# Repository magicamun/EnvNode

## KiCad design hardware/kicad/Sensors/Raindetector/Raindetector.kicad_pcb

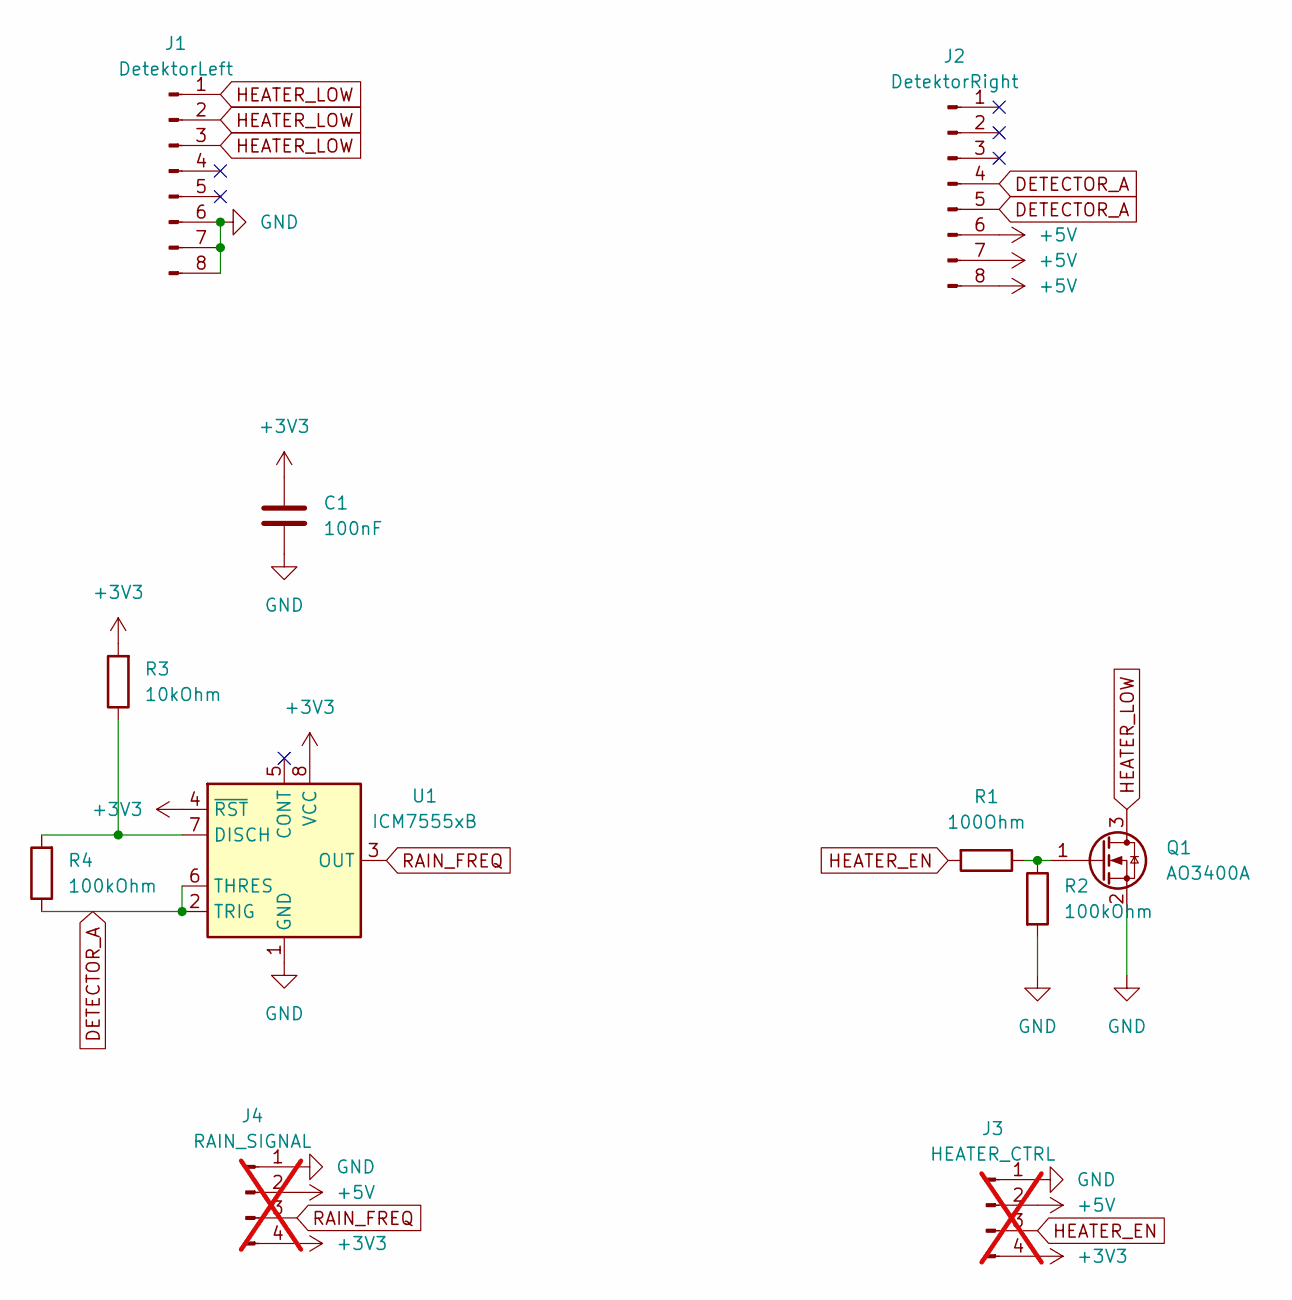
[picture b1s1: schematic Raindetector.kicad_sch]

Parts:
C1: 100nF; C_1206_3216Metric_Pad1.33x1.80mm_HandSolder
J1: DetektorLeft; PinHeader_1x08_P2.54mm_Vertical
J2: DetektorRight; PinHeader_1x08_P2.54mm_Vertical
J3: HEATER_CTRL; PinHeader_1x04_P2.54mm_Vertical; not fitted
J4: RAIN_SIGNAL; PinHeader_1x04_P2.54mm_Vertical; not fitted
Q1: AO3400A; SOT-23
R1: 100Ohm; R_1206_3216Metric_Pad1.30x1.75mm_HandSolder
R2, R4: 100kOhm; R_1206_3216Metric_Pad1.30x1.75mm_HandSolder
R3: 10kOhm; R_1206_3216Metric_Pad1.30x1.75mm_HandSolder
U1: ICM7555xB; SOIC-8_3.9x4.9mm_P1.27mm

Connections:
+3V3: C1.1, J3.4, J4.4, R3.2, U1.4 (~RST), U1.8 (VCC)
+5V: J2.6, J2.7, J2.8, J3.2, J4.2
DETECTOR_A: J2.4, J2.5, R4.1, U1.2 (TRIG), U1.6 (THRES)
GND: C1.2, J1.6, J1.7, J1.8, J3.1, J4.1, Q1.2 (S), R2.2, U1.1 (GND)
HEATER_EN: J3.3, R1.2
HEATER_LOW: J1.1, J1.2, J1.3, Q1.3 (D)
unnamed: Q1.1 (G), R1.1, R2.1
unnamed: R3.1, R4.2, U1.7 (DISCH)
RAIN_FREQ: J4.3, U1.3 (OUT)

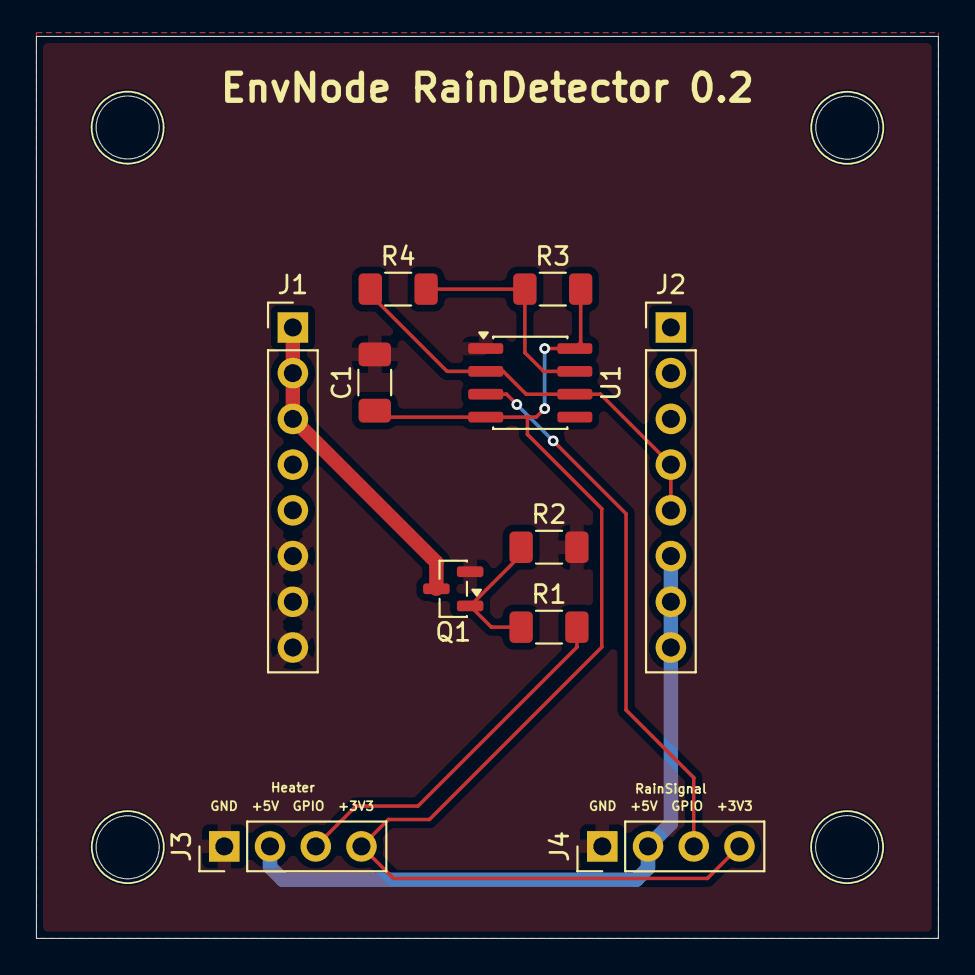
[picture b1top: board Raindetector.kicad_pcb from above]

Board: 2 copper layers, 50.1 x 50.1 mm, 11 parts (0 on the bottom side), 9 nets.

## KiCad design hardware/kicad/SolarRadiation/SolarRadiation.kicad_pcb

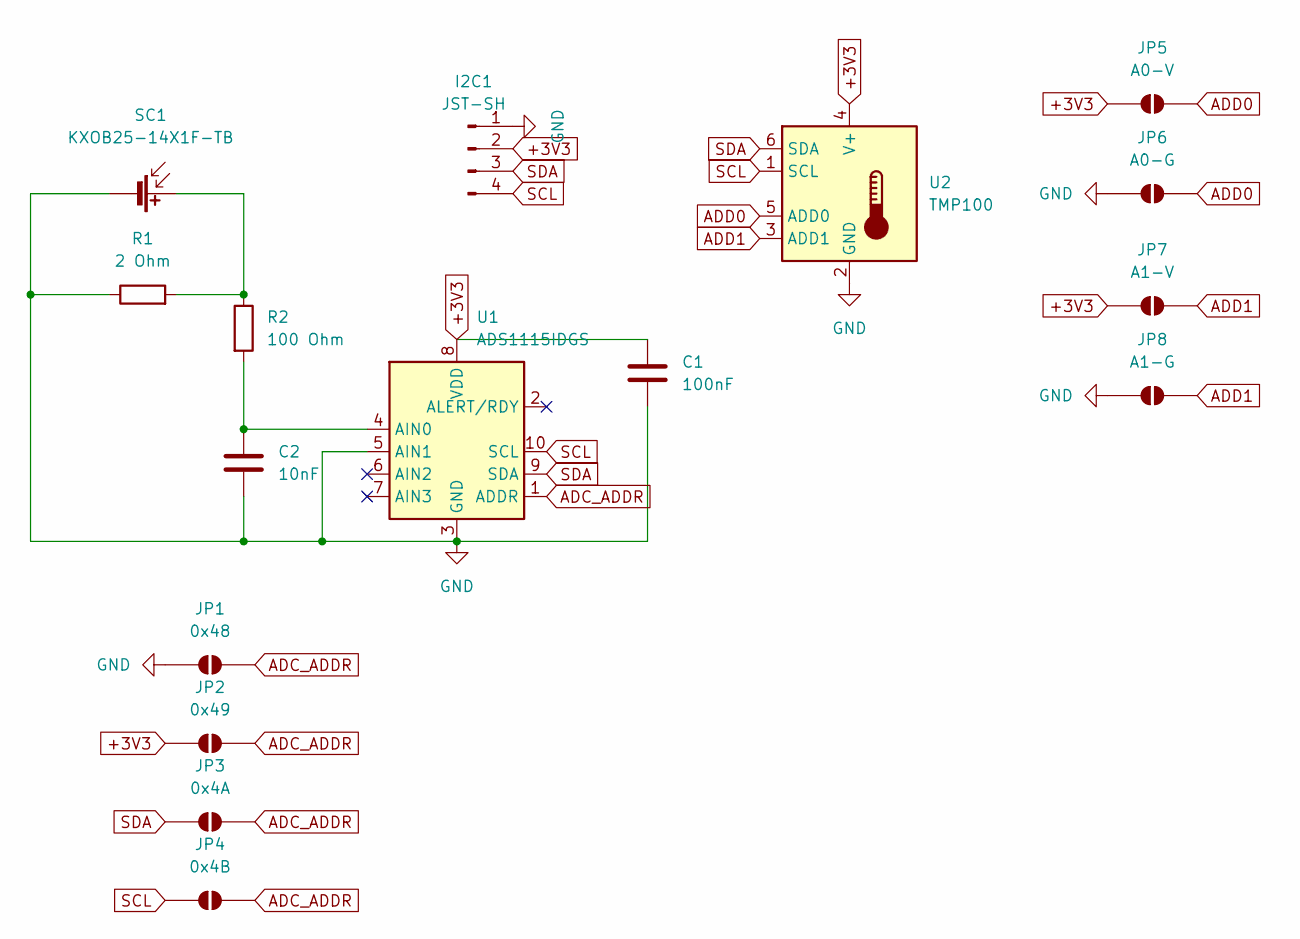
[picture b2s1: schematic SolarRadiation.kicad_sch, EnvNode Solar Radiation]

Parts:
C1: 100nF; C_1206_3216Metric_Pad1.33x1.80mm_HandSolder
C2: 10nF; C_1206_3216Metric_Pad1.33x1.80mm_HandSolder
I2C1: JST-SH; JST_SH_SM04B-SRSS-TB_1x04-1MP_P1.00mm_Horizontal
JP1: 0x48; SolderJumper-2_P1.3mm_Open_Pad1.0x1.5mm
JP2: 0x49; SolderJumper-2_P1.3mm_Open_Pad1.0x1.5mm
JP3: 0x4A; SolderJumper-2_P1.3mm_Open_Pad1.0x1.5mm
JP4: 0x4B; SolderJumper-2_P1.3mm_Open_Pad1.0x1.5mm
JP5: A0-V; SolderJumper-2_P1.3mm_Open_Pad1.0x1.5mm
JP6: A0-G; SolderJumper-2_P1.3mm_Open_Pad1.0x1.5mm
JP7: A1-V; SolderJumper-2_P1.3mm_Open_Pad1.0x1.5mm
JP8: A1-G; SolderJumper-2_P1.3mm_Open_Pad1.0x1.5mm
R1: 2 Ohm; R_1206_3216Metric_Pad1.30x1.75mm_HandSolder
R2: 100 Ohm; R_1206_3216Metric_Pad1.30x1.75mm_HandSolder
SC1: KXOB25-14X1F-TB; KXOB25-14X1F
U1: ADS1115IDGS; TSSOP-10_3x3mm_P0.5mm
U2: TMP100; SOT-23-6

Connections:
+3V3: C1.1, I2C1.2, JP2.1 (A), JP5.1 (A), JP7.1 (A), U1.8 (VDD), U2.4 (V+)
ADC_ADDR: JP1.2 (B), JP2.2 (B), JP3.2 (B), JP4.2 (B), U1.1 (ADDR)
ADD0: JP5.2 (B), JP6.2 (B), U2.5 (ADD0)
ADD1: JP7.2 (B), JP8.2 (B), U2.3 (ADD1)
GND: C1.2, C2.2, I2C1.1, JP1.1 (A), JP6.1 (A), JP8.1 (A), R1.1, SC1.2 (-), U1.3 (GND), U1.5 (AIN1), U2.2 (GND)
unnamed: R1.2, R2.1, SC1.1 (+)
unnamed: C2.1, R2.2, U1.4 (AIN0)
SCL: I2C1.4, JP4.1 (A), U1.10 (SCL), U2.1 (SCL)
SDA: I2C1.3, JP3.1 (A), U1.9 (SDA), U2.6 (SDA)

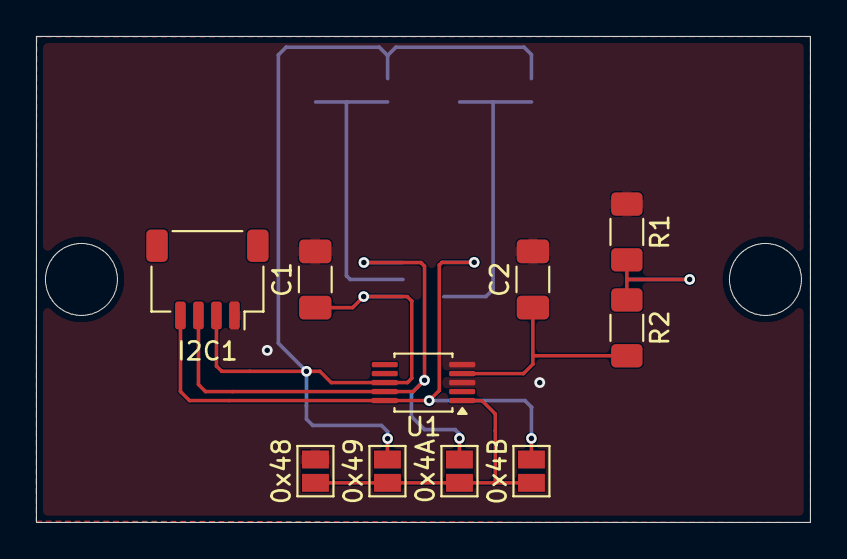
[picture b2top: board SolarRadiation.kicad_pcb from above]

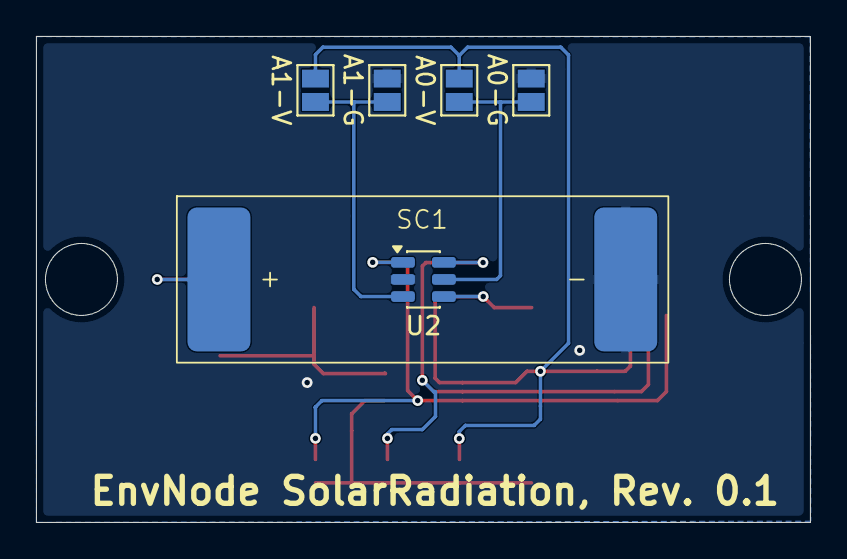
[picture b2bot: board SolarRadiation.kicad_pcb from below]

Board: 2 copper layers, 43.0 x 27.0 mm, 16 parts (6 on the bottom side), 9 nets.

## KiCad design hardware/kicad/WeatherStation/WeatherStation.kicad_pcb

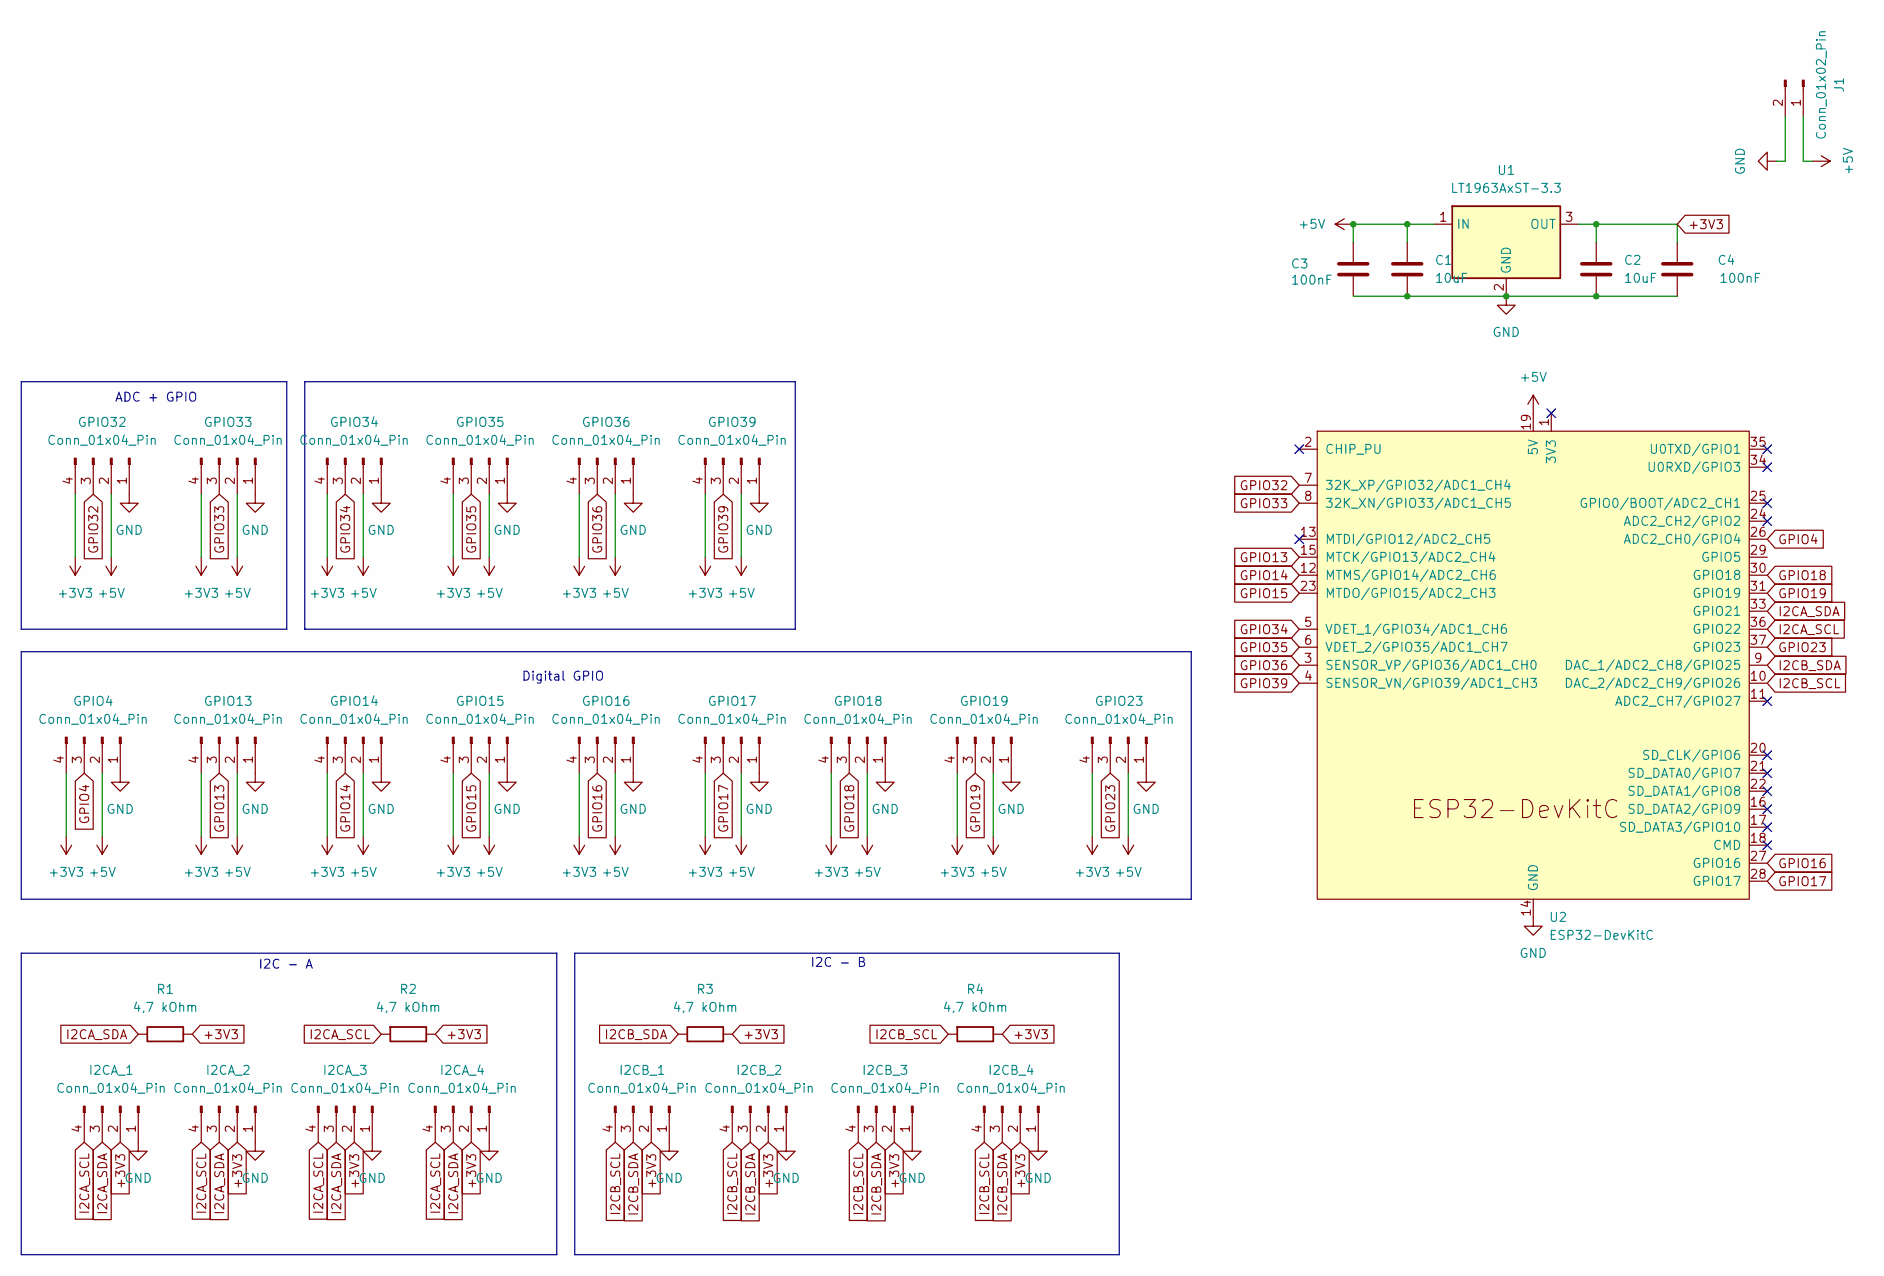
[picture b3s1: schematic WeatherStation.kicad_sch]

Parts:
C1, C2: 10uF; C_1206_3216Metric_Pad1.33x1.80mm_HandSolder
C3, C4: 100nF; C_1206_3216Metric_Pad1.33x1.80mm_HandSolder
GPIO4, GPIO13, GPIO14, GPIO15, GPIO16, GPIO17, GPIO18, GPIO19, GPIO23, GPIO32, GPIO33, GPIO34, GPIO35, GPIO36, GPIO39: Conn_01x04_Pin; JST_PH_B4B-PH-K_1x04_P2.00mm_Vertical
I2CA_1, I2CA_2, I2CA_3, I2CB_1, I2CB_2, I2CB_3: Conn_01x04_Pin; JST_SH_SM04B-SRSS-TB_1x04-1MP_P1.00mm_Horizontal
I2CA_4, I2CB_4: Conn_01x04_Pin; QWIIC_PinSocket_1x04_P2.54mm_Vertical
J1: Conn_01x02_Pin; JST_PH_B2B-PH-K_1x02_P2.00mm_Vertical
R1, R2, R3, R4: 4,7 kOhm; R_1206_3216Metric_Pad1.30x1.75mm_HandSolder
U1: LT1963AxST-3.3; SOT-223-3_TabPin2
U2: ESP32-DevKitC

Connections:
+3V3: C2.1, C4.2, GPIO4.4, GPIO13.4, GPIO14.4, GPIO15.4, GPIO16.4, GPIO17.4, GPIO18.4, GPIO19.4, GPIO23.4, GPIO32.4, GPIO33.4, GPIO34.4, GPIO35.4, GPIO36.4, GPIO39.4, I2CA_1.2, I2CA_2.2, I2CA_3.2, I2CA_4.2, I2CB_1.2, I2CB_2.2, I2CB_3.2, I2CB_4.2, R1.2, R2.1, R3.2, R4.1, U1.3 (OUT)
+5V: C1.1, C3.2, GPIO4.2, GPIO13.2, GPIO14.2, GPIO15.2, GPIO16.2, GPIO17.2, GPIO18.2, GPIO19.2, GPIO23.2, GPIO32.2, GPIO33.2, GPIO34.2, GPIO35.2, GPIO36.2, GPIO39.2, J1.1, U1.1 (IN), U2.19 (5V)
GND: C1.2, C2.2, C3.1, C4.1, GPIO4.1, GPIO13.1, GPIO14.1, GPIO15.1, GPIO16.1, GPIO17.1, GPIO18.1, GPIO19.1, GPIO23.1, GPIO32.1, GPIO33.1, GPIO34.1, GPIO35.1, GPIO36.1, GPIO39.1, I2CA_1.1, I2CA_2.1, I2CA_3.1, I2CA_4.1, I2CB_1.1, I2CB_2.1, I2CB_3.1, I2CB_4.1, J1.2, U1.2 (GND), U2.14 (GND), U2.32 (GND), U2.38 (GND)
GPIO4: GPIO4.3, U2.26 (ADC2_CH0/GPIO4)
GPIO13: GPIO13.3, U2.15 (MTCK/GPIO13/ADC2_CH4)
GPIO14: GPIO14.3, U2.12 (MTMS/GPIO14/ADC2_CH6)
GPIO15: GPIO15.3, U2.23 (MTDO/GPIO15/ADC2_CH3)
GPIO16: GPIO16.3, U2.27 (GPIO16)
GPIO17: GPIO17.3, U2.28 (GPIO17)
GPIO18: GPIO18.3, U2.30 (GPIO18)
GPIO19: GPIO19.3, U2.31 (GPIO19)
GPIO23: GPIO23.3, U2.37 (GPIO23)
GPIO32: GPIO32.3, U2.7 (32K_XP/GPIO32/ADC1_CH4)
GPIO33: GPIO33.3, U2.8 (32K_XN/GPIO33/ADC1_CH5)
GPIO34: GPIO34.3, U2.5 (VDET_1/GPIO34/ADC1_CH6)
GPIO35: GPIO35.3, U2.6 (VDET_2/GPIO35/ADC1_CH7)
GPIO36: GPIO36.3, U2.3 (SENSOR_VP/GPIO36/ADC1_CH0)
GPIO39: GPIO39.3, U2.4 (SENSOR_VN/GPIO39/ADC1_CH3)
I2CA_SCL: I2CA_1.4, I2CA_2.4, I2CA_3.4, I2CA_4.4, R2.2, U2.36 (GPIO22)
I2CA_SDA: I2CA_1.3, I2CA_2.3, I2CA_3.3, I2CA_4.3, R1.1, U2.33 (GPIO21)
I2CB_SCL: I2CB_1.4, I2CB_2.4, I2CB_3.4, I2CB_4.4, R4.2, U2.10 (DAC_2/ADC2_CH9/GPIO26)
I2CB_SDA: I2CB_1.3, I2CB_2.3, I2CB_3.3, I2CB_4.3, R3.1, U2.9 (DAC_1/ADC2_CH8/GPIO25)

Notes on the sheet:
ADC + GPIO
I2C - A
I2C - B
Digital GPIO

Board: 2 copper layers, 34 parts (0 on the bottom side), 22 nets, no tracks yet.
